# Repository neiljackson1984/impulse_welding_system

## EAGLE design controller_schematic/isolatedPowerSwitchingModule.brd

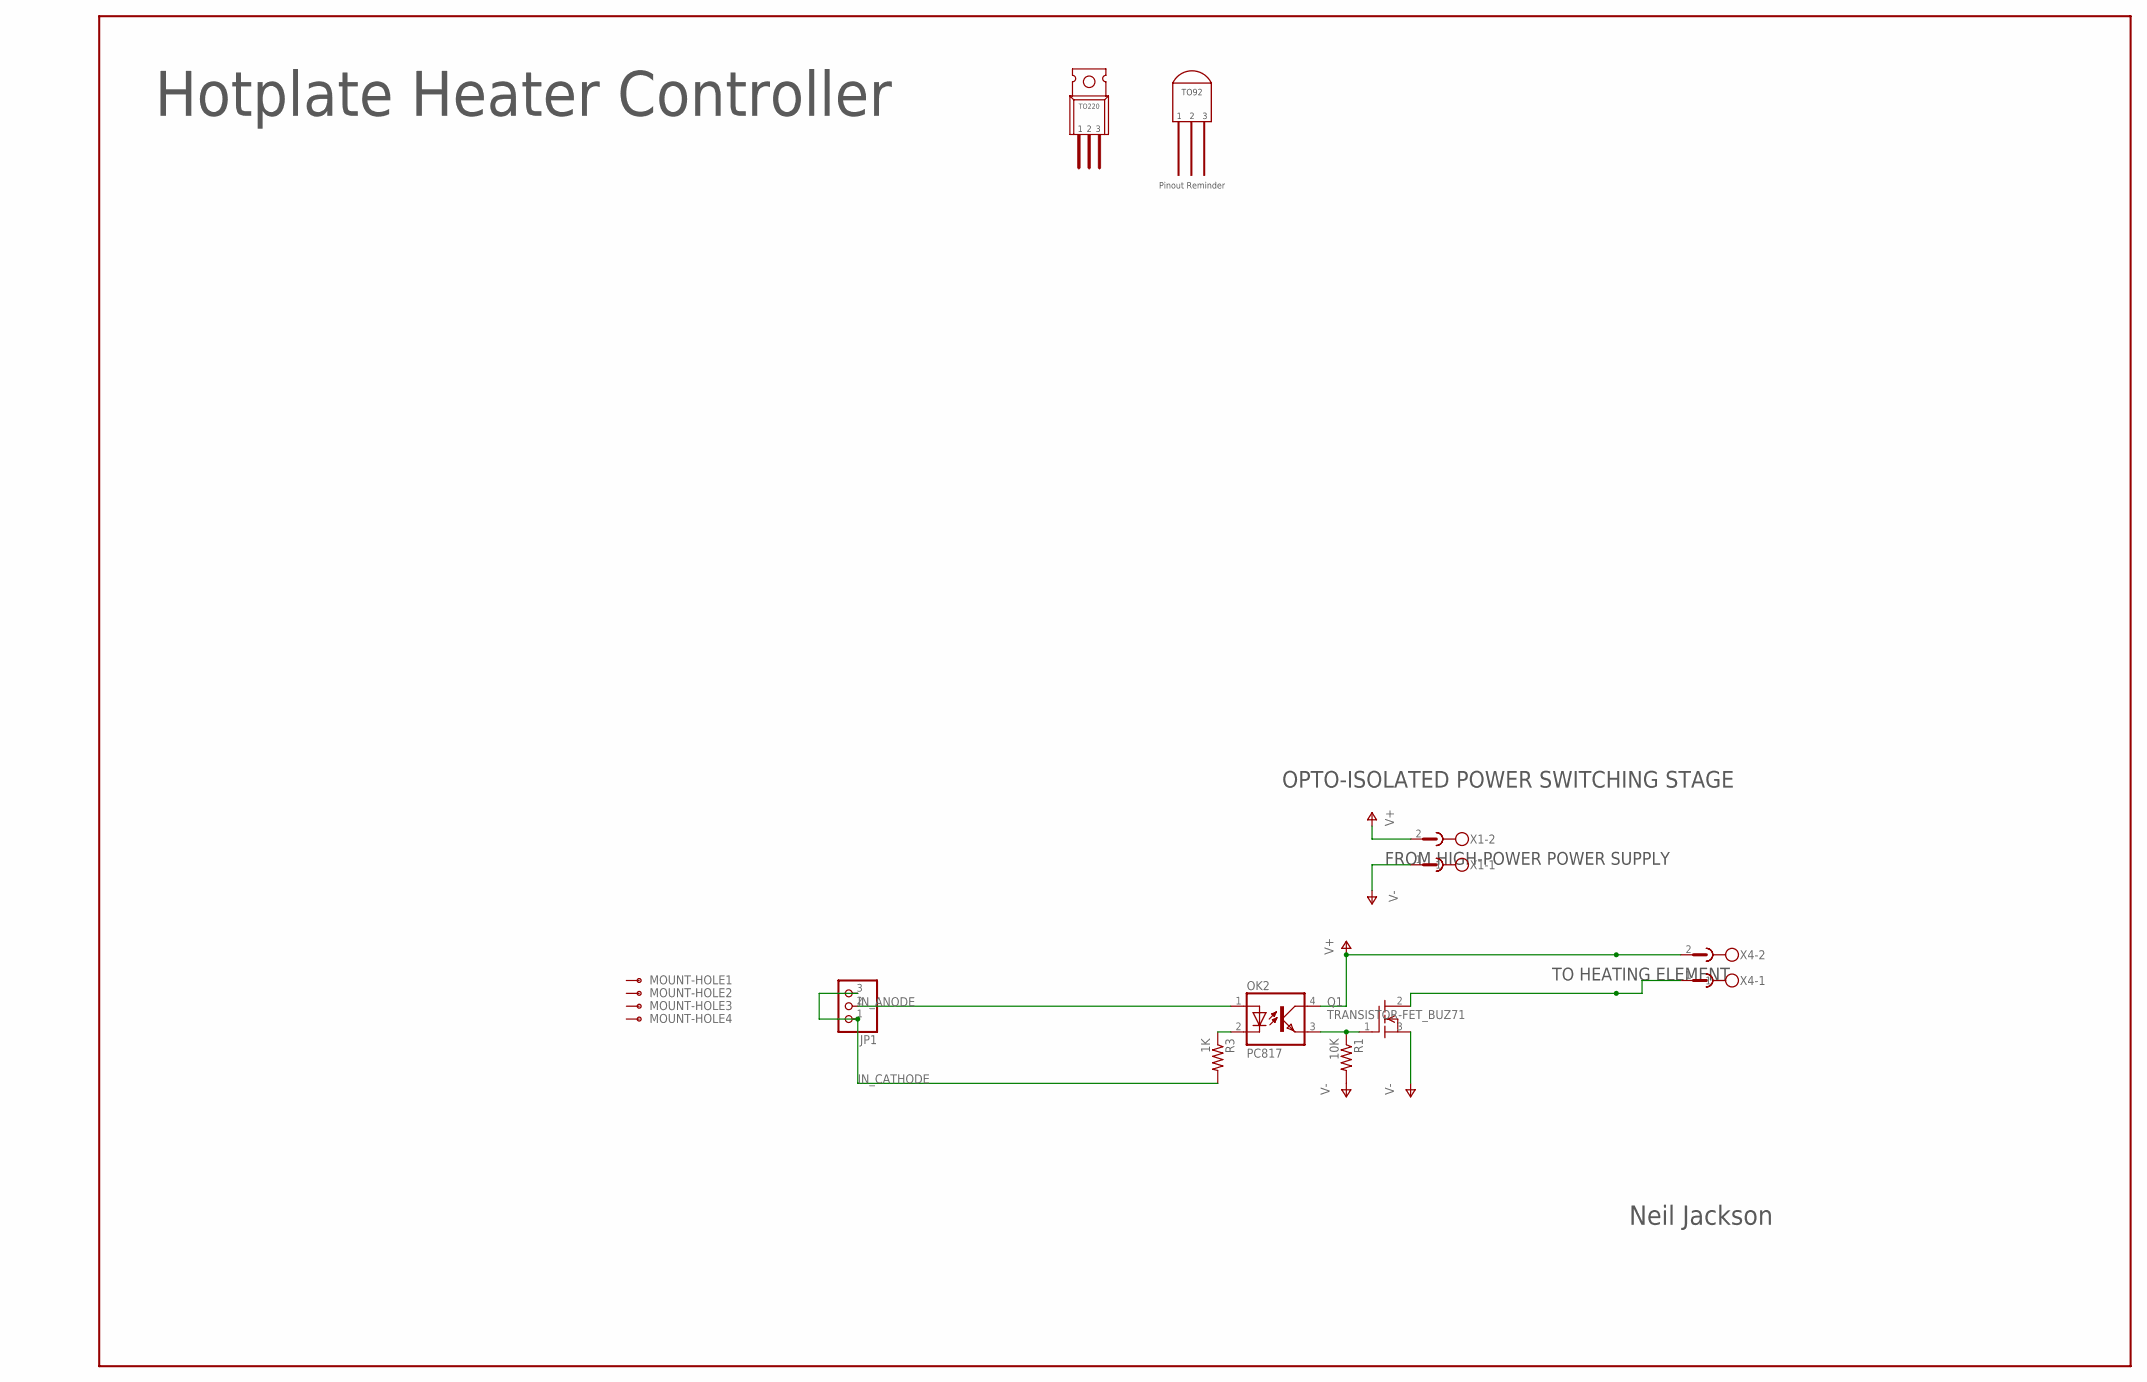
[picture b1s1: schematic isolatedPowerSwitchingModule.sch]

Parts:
JP1: PINHD-1X3; 1X03
MOUNT-HOLE1, MOUNT-HOLE2, MOUNT-HOLE3, MOUNT-HOLE4: MOUNT-HOLE; 8-32
OK2: PC817; DIL04
Q1: TRANSISTOR-FET_BUZ71; TRANSISTOR-FET_TO220
R1: 10K; 0207/10
R3: 1K; 0207/10
X1, X4: PIN_HEADER_2_CONDUCTORRIGHTANGLE; MSTBA2

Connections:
IN_ANODE: JP1.2, OK2.1 (A)
IN_CATHODE: JP1.1, JP1.3, R3.2
unnamed: Q1.2 (D), X4.1
unnamed: OK2.3 (EMIT), Q1.1 (G), R1.1
unnamed: OK2.2 (C), R3.1
V+: OK2.4 (COL), X1.2, X4.2
V-: Q1.3 (S), R1.2, X1.1

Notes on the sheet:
TO HEATING ELEMENT
Hotplate Heater Controller
Neil Jackson
FROM HIGH-POWER POWER SUPPLY
OPTO-ISOLATED POWER SWITCHING STAGE

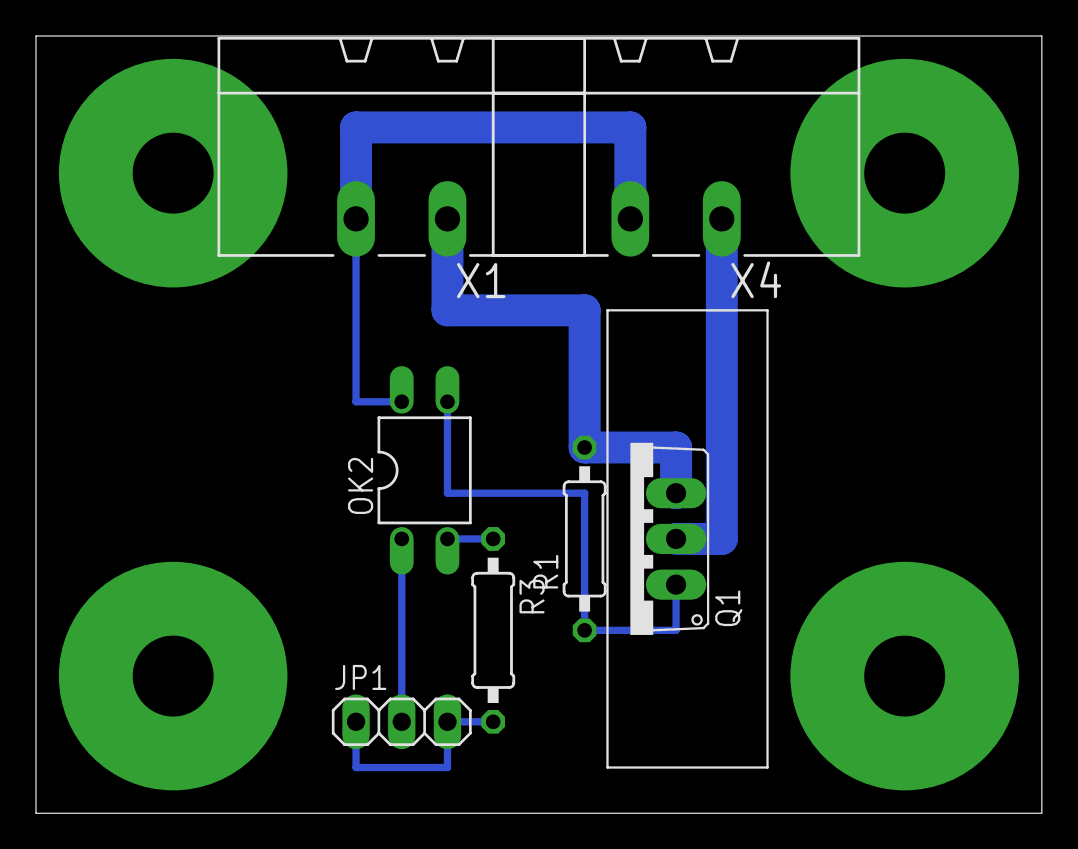
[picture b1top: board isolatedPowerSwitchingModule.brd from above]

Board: 2 copper layers, 55.9 x 43.2 mm, 11 parts (0 on the bottom side), 7 nets.

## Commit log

2017-08-26 Braid: Add mirror 'heater_controller_firmware/braids/Button' at 'ef8a321'
2017-08-27 fixed the conversion of 32-bit ints to strings. Got interrupts working to detect button presses reliably.
2017-08-28 interrupt-based pulse timer is working reasonably well.
2017-09-18 checkpoint
2017-09-18 Braid: Add mirror 'sealer_bar_3d_model/braids/design_framework' at 'a431982'
2017-09-19 tensioning concept model created
2017-09-25 added springs.
2017-10-08 fixing the braid file after realizing that braids does not fully support subdirectories.
2017-10-08 added .SILENT to makefile to suppress makefile comments from being displayed on the output from the makefile.
2017-10-10 made the spring flexible.
2018-03-12 checkpoint. (seems like I forgot to commit last time I was working on this project).
